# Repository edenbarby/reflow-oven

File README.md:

# reflow-oven
A DIY reflow oven with a little inspiration from the internet.

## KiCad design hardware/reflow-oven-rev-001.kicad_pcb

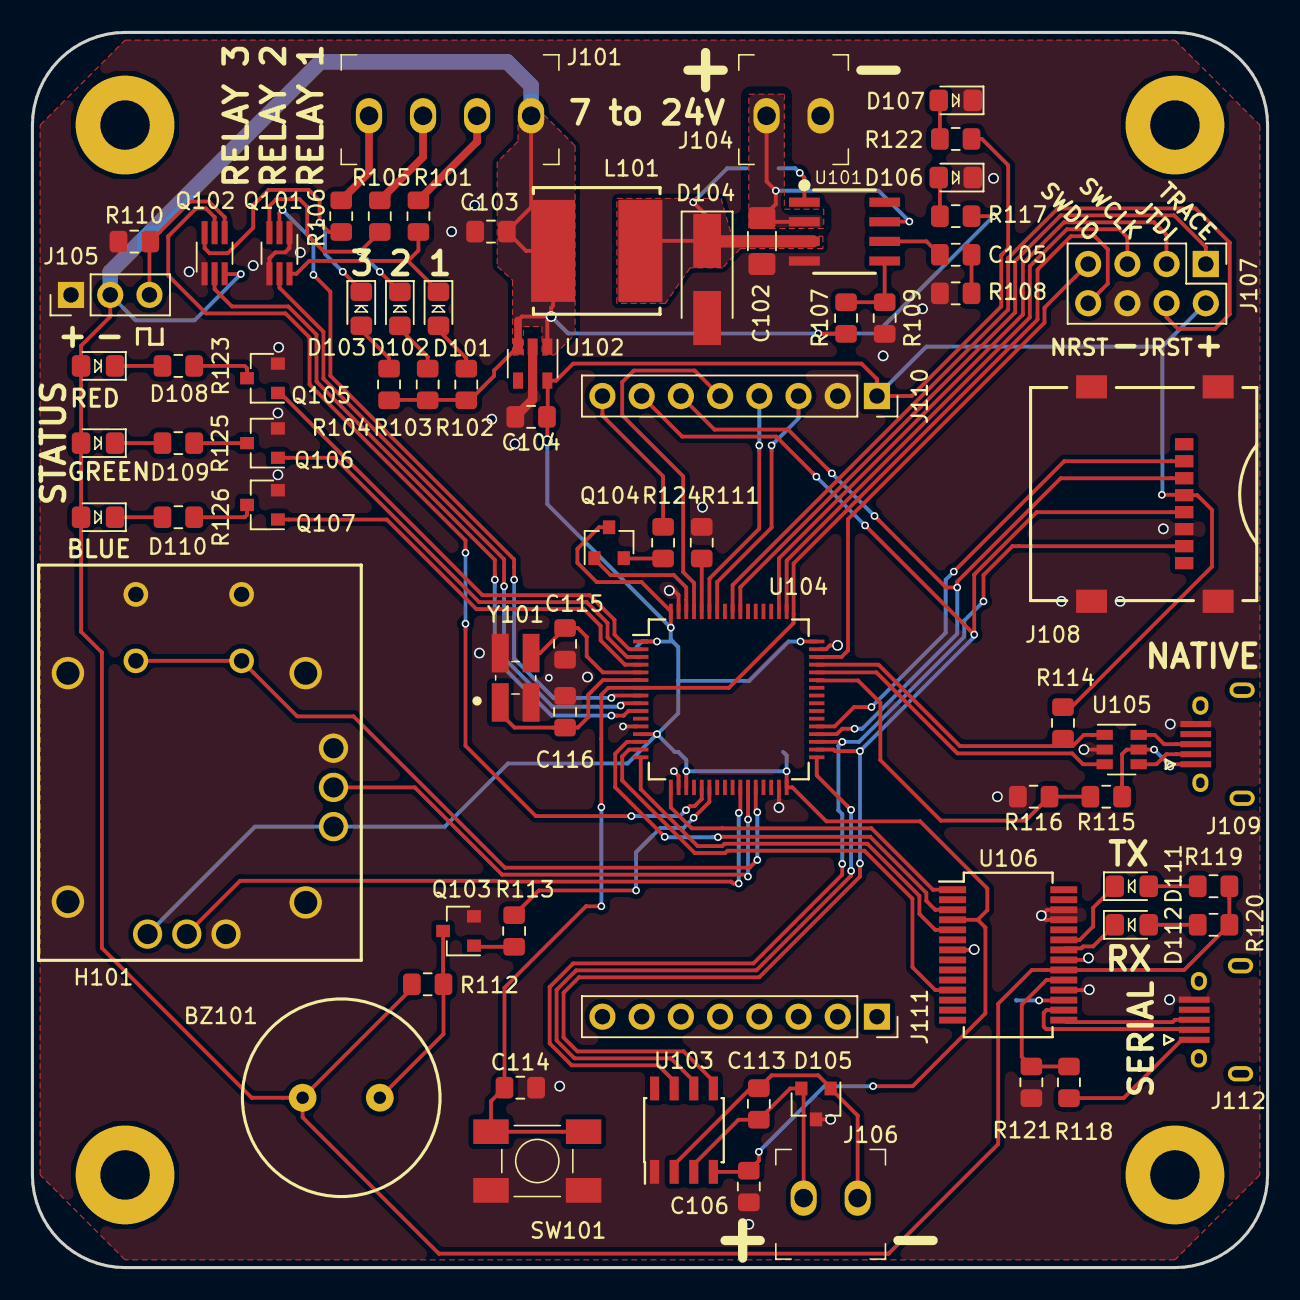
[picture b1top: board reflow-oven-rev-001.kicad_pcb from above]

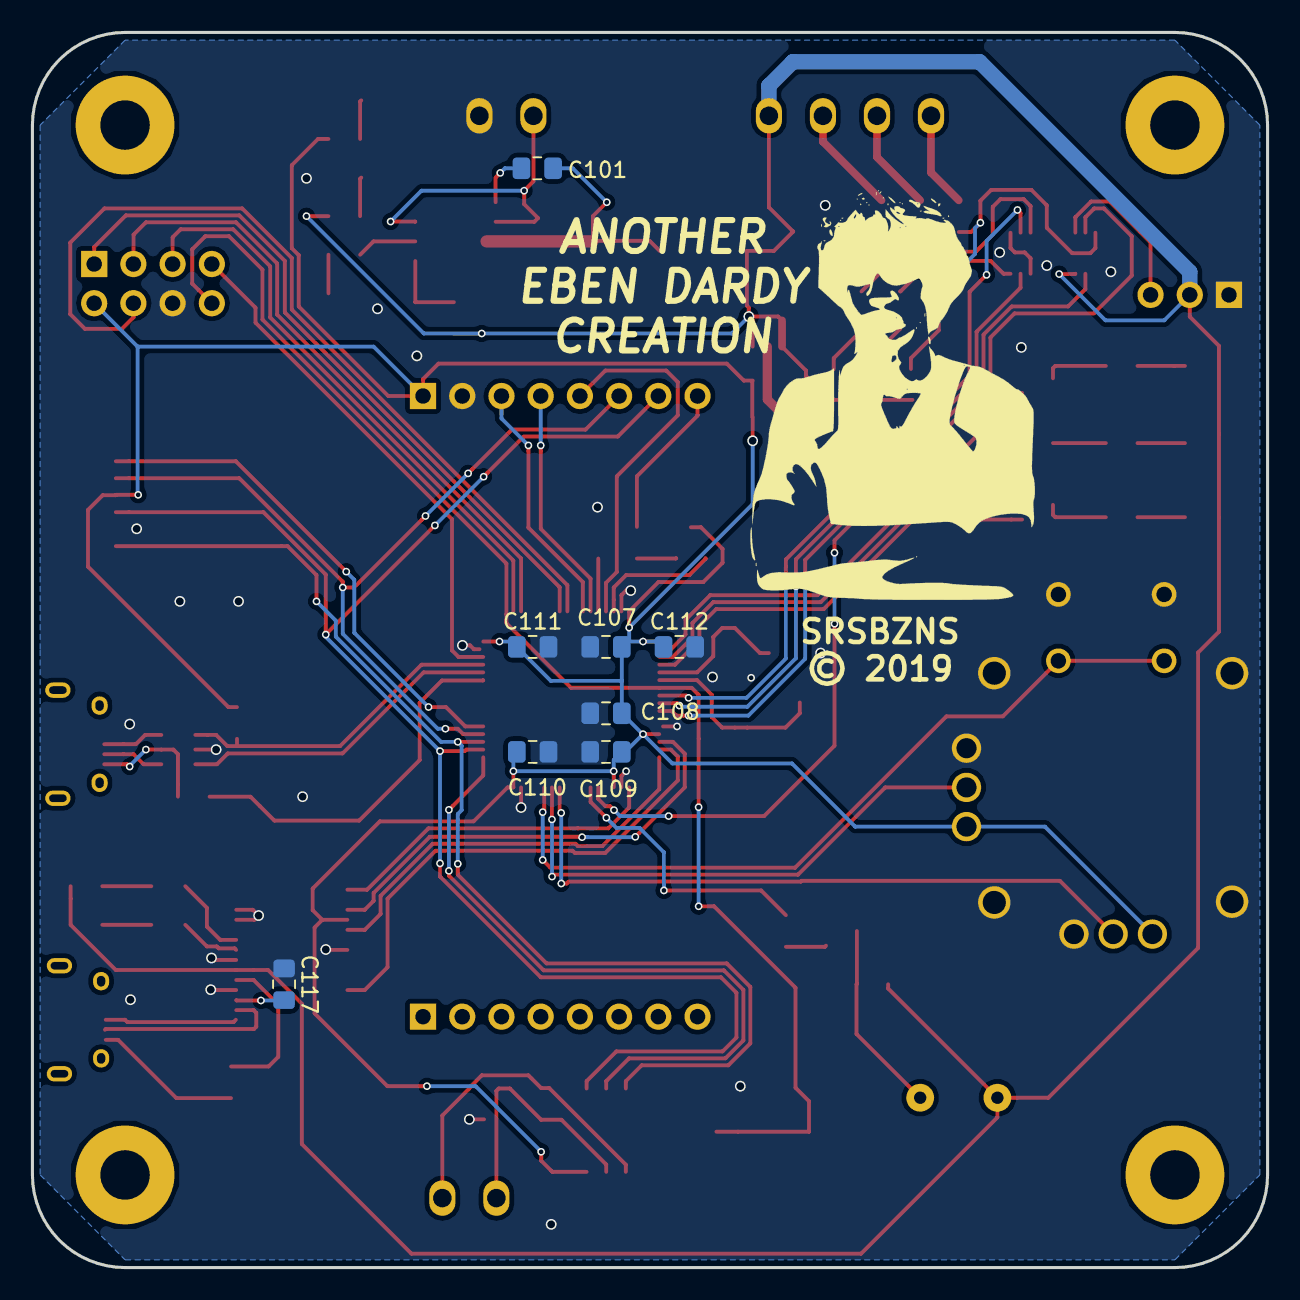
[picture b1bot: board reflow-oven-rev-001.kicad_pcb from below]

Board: 2 copper layers, 80.0 x 80.0 mm, 87 parts (8 on the bottom side), 81 nets.

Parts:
BZ101: Piezo Buzzer; PKM13EPYH4000-A0
C101, C113: 10n, 50V; C_0805_2012Metric_Pad1.15x1.40mm_HandSolder
C102: 10u, 50V; C_1206_3216Metric_Pad1.42x1.75mm_HandSolder
C103, C104: 4u7, 25V; C_0805_2012Metric_Pad1.15x1.40mm_HandSolder
C105: 2n2, 50V; C_0805_2012Metric_Pad1.15x1.40mm_HandSolder
C106, C107, C108, C109, C110, C111, C112, C114, C117: 100n; C_0805_2012Metric_Pad1.15x1.40mm_HandSolder
C115, C116: 10p; C_0805_2012Metric_Pad1.15x1.40mm_HandSolder
D101, D102, D103, D106, D107, D108: LED Red; LED_0805_2012Metric_Pad1.15x1.40mm_HandSolder
D104: Schottky, 40V, 3A; D_SMA_Handsoldering
D105: NUP2105L; SOT-23
D109, D111: LED Green; LED_0805_2012Metric_Pad1.15x1.40mm_HandSolder
D110, D112: LED Blue; LED_0805_2012Metric_Pad1.15x1.40mm_HandSolder
H101: Joystick; COM-09032
J101: Relays; Connector_Pheonix_WTB_Screw_3.5mm_4X1
J104: Power In; Connector_Pheonix_WTB_Screw_3.5mm_2X1
J105: Servo; PinHeader_1x03_P2.54mm_Vertical
J106: Thermocouple; Connector_Pheonix_WTB_Screw_3.5mm_2X1
J107: JTAG, SWD; PinHeader_2x04_P2.54mm_Vertical
J108: Micro SD Card; MEM2067-02-180-00-A
J109: USB Native; USB_Micro-B_Amphenol_10118194-0X0XLF
J110, J111: LCD 10168; PinSocket_1x08_P2.54mm_Vertical
J112: USB Serial; USB_Micro-B_Amphenol_10118194-0X0XLF
L101: 15u, 3.6A; SRN8040TA-150M
MH101, MH102, MH103, MH104: MountingHole; MountingHole_3.2mm_M3_Pad
Q101, Q102: SSM6N7002KFU; SOT-363_SC-70-6_Handsoldering
Q103, Q104, Q105, Q106, Q107: MMBT3904; SOT-23
R101, R102, R103, R104, R105, R106, R117, R119, R120, R122, R123, R124, R125, R126: 270R; R_0805_2012Metric_Pad1.15x1.40mm_HandSolder
R107, R108, R111, R121: 15k; R_0805_2012Metric_Pad1.15x1.40mm_HandSolder
R109, R110, R118: 5k6; R_0805_2012Metric_Pad1.15x1.40mm_HandSolder
R112, R113, R114: 1k5; R_0805_2012Metric_Pad1.15x1.40mm_HandSolder
R115, R116: 100k; R_0805_2012Metric_Pad1.15x1.40mm_HandSolder
SW101: Push Button; SW_SPST_CK_PTS647_4.5mm
U101: ACT4060A
U102: MIC5504-3.3YM5; SOT-23-5
U103: MAX31855KASA; SOIC-8_3.9x4.9mm_P1.27mm
U104: STM32F302R8Tx; LQFP-64_10x10mm_P0.5mm
U105: USBLC6-2SC6; SOT-23-6
U106: FT232RL; SSOP-28_5.3x10.2mm_P0.65mm
Y101: 12MHz; Crystal_SMD_2520-4Pin_2.5x2.0mm_HandSoldering

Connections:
+3V3: C104.1, C106.1, C107.1, C108.1, C109.1, C110.1, C111.1, C112.1, H101.1, H101.4, J107.2, J108.4, J110.1, Q104.3, R114.1, R122.1, U102.5, U103.4, U104.1, U104.13, U104.19, U104.32, U104.48, U104.64, U106.4
+5V: BZ101.1, C103.1, D108.2, D109.2, D110.2, J101.1, J105.2, L101.2, Q102.3, R102.1, R103.1, R104.1, R107.1, R112.1, R117.1, R119.1, R120.1, U102.1, U102.3, U106.20
/BUZZER: R113.2, U104.22
/FTDI_CTS: U104.15, U106.11
/FTDI_RTS: U104.14, U106.3
/FTDI_RX: U104.16, U106.5
/FTDI_TX: U104.17, U106.1
/JOYSTICK_BTN: H101.7, U104.28
/JOYSTICK_X: H101.2, U104.26
/JOYSTICK_Y: H101.5, U104.27
/JTCK_SWCLK: J107.5, U104.49
/JTDI: J107.3, U104.50
/JTDO_TRACESWO: J107.1, U104.55
/JTMS_SWDIO: J107.7, U104.46
/JTRST: J107.4, U104.56
/LCD_LED: Q104.1, U104.62
/LCD_MODE: J110.5, U104.61
/LCD_MOSI: J108.3, J110.6, U104.36
/LCD_SCLK: J108.5, J110.7, U103.5, U104.34
/LED_1: Q105.1, U104.2
/LED_2: Q106.1, U104.3
/LED_3: Q107.1, U104.4
/NRST: C114.1, J107.8, SW101.2, U104.7
/RELAY_1: Q101.2, U104.8
/RELAY_2: Q101.5, U104.9
/RELAY_3: Q102.2, U104.10
/RELAY_RET_1: J101.2, R101.2
/RELAY_RET_2: J101.3, R105.2
/SD_MISO: J108.7, U103.7, U104.35
/SERVO: Q102.5, U104.21
/USB_D+: R114.2, U104.45, U105.1
/USB_D-: U104.44, U105.3
/USB_VBUS_SENSE: R115.2, R116.1, U104.43
/~LCD_CS: J110.3, U104.58
/~LCD_RST: J110.4, U104.59
/~SD_CS: J108.2, U104.37
/~TC_CS: U103.6, U104.33
GND: C102.2, C103.2, C104.2, C106.2, C107.2, C108.2, C109.2, C110.2, C111.2, C112.2, C114.2, C115.2, C116.1, C117.1, D104.2, D105.3, D106.1, D107.1, H101.3, H101.6, H101.8, H101.9, J104.1, J105.1, J107.6, J108.6, J108.9, J109.5, J110.2, J112.5, Q101.1, Q101.4, Q102.1, Q103.2, Q105.2, Q106.2, Q107.2, R108.2, R109.2, R110.2, R111.2, R116.2, R121.2, SW101.1, U101.4, U102.2, U103.1, U104.12, U104.18, U104.31, U104.47, U104.63, U105.2, U106.7, U106.18, U106.21, U106.25, U106.26, Y101.2, Y101.4
unnamed: BZ101.2, Q103.3, R112.2
unnamed: C101.1, U101.1
unnamed: C101.2, D104.1, L101.1, U101.3
unnamed: C102.1, J104.2, U101.2, U101.7
unnamed: C105.1, U101.6
unnamed: C105.2, R108.1
unnamed: C113.1, D105.2, J106.1, U103.3
unnamed: C113.2, D105.1, J106.2, U103.2
unnamed: C115.1, U104.5, Y101.3
unnamed: C116.2, U104.6, Y101.1
unnamed: C117.2, U106.17
unnamed: D101.1, Q101.6, R101.1
unnamed: D101.2, R102.2
unnamed: D102.1, Q101.3, R105.1
unnamed: D102.2, R103.2
unnamed: D103.1, Q102.6, R106.1
unnamed: D103.2, R104.2
unnamed: D106.2, R117.2
unnamed: D107.2, R122.2
unnamed: D108.1, R123.1
unnamed: D109.1, R125.1
unnamed: D110.1, R126.1
unnamed: D111.1, U106.23
unnamed: D111.2, R119.2
unnamed: D112.1, U106.22
unnamed: D112.2, R120.2
unnamed: J101.4, R106.2
unnamed: J105.3, Q102.4, R110.1
unnamed: J109.2, U105.4
unnamed: J109.3, U105.6
unnamed: J110.8, R124.2
unnamed: J112.1, R118.1
unnamed: J112.2, U106.16
unnamed: J112.3, U106.15
unnamed: Q103.1, R113.1
unnamed: Q104.2, R124.1
unnamed: Q105.3, R123.2
unnamed: Q106.3, R125.2
unnamed: Q107.3, R126.2
unnamed: R107.2, R109.1, U101.5
unnamed: R111.1, U104.60
unnamed: R118.2, R121.1, U106.19
VBUS: J109.1, R115.1, U105.5

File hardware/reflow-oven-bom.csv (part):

"Source:","D:\repo\reflow-oven\hardware\reflow-oven-rev-001.sch"
"Date:","18/09/2019 8:32:10 AM"
"Tool:","Eeschema (5.0.0)"
"Generator:","D:\Program Files\KiCad\bin\scripting\plugins/bom_csv_grouped_by_value.py"
"Component Count:","87"

"Individual Components:"

"Item","Qty","Reference(s)","Value","LibPart","Footprint","Datasheet","Description","Digi-Key Part Number"
"","","BZ101","Piezo Buzzer","Device:Buzzer","my-library:PKM13EPYH4000-A0","","AUDIO PIEZO TRANSDUCER 30V TH","490-4698-1-ND"
"","","C101","10n, 50V","Device:C","Capacitor_SMD:C_0805_2012Metric_Pad1.15x1.40mm_HandSolder","","CAP CER 10000PF 50V X7R 0805","1276-1015-1-ND"
"","","C102","10u, 50V","Device:C","Capacitor_SMD:C_1206_3216Metric_Pad1.42x1.75mm_HandSolder","","CAP CER 10UF 50V X5R 1206","1276-6736-1-ND"
"","","C103","4u7, 25V","Device:C","Capacitor_SMD:C_0805_2012Metric_Pad1.15x1.40mm_HandSolder","","CAP CER 4.7UF 25V X5R 0805","732-7628-1-ND"
"","","C104","4u7, 25V","Device:C","Capacitor_SMD:C_0805_2012Metric_Pad1.15x1.40mm_HandSolder","","CAP CER 4.7UF 25V X5R 0805","732-7628-1-ND"
"","","C105","2n2, 50V","Device:C","Capacitor_SMD:C_0805_2012Metric_Pad1.15x1.40mm_HandSolder","","CAP CER 2200PF 50V X7R 0805","399-1151-1-ND"
"","","C106","100n","Device:C_Small","Capacitor_SMD:C_0805_2012Metric_Pad1.15x1.40mm_HandSolder","","CAP CER 0.1UF 50V X7R 0805","1276-2450-1-ND"
"","","C107","100n","Device:C_Small","Capacitor_SMD:C_0805_2012Metric_Pad1.15x1.40mm_HandSolder","","CAP CER 0.1UF 50V X7R 0805","1276-2450-1-ND"
"","","C108","100n","Device:C_Small","Capacitor_SMD:C_0805_2012Metric_Pad1.15x1.40mm_HandSolder","","CAP CER 0.1UF 50V X7R 0805","1276-2450-1-ND"
"","","C109","100n","Device:C_Small","Capacitor_SMD:C_0805_2012Metric_Pad1.15x1.40mm_HandSolder","","CAP CER 0.1UF 50V X7R 0805","1276-2450-1-ND"
"","","C110","100n","Device:C_Small","Capacitor_SMD:C_0805_2012Metric_Pad1.15x1.40mm_HandSolder","","CAP CER 0.1UF 50V X7R 0805","1276-2450-1-ND"
"","","C111","100n","Device:C_Small","Capacitor_SMD:C_0805_2012Metric_Pad1.15x1.40mm_HandSolder","","CAP CER 0.1UF 50V X7R 0805","1276-2450-1-ND"
"","","C112","100n","Device:C_Small","Capacitor_SMD:C_0805_2012Metric_Pad1.15x1.40mm_HandSolder","","CAP CER 0.1UF 50V X7R 0805","1276-2450-1-ND"
"","","C113","10n, 50V","Device:C_Small","Capacitor_SMD:C_0805_2012Metric_Pad1.15x1.40mm_HandSolder","","CAP CER 10000PF 50V X7R 0805","1276-1015-1-ND"
"","","C114","100n","Device:C_Small","Capacitor_SMD:C_0805_2012Metric_Pad1.15x1.40mm_HandSolder","","CAP CER 0.1UF 50V X7R 0805","1276-2450-1-ND"
"","","C115","10p","Device:C_Small","Capacitor_SMD:C_0805_2012Metric_Pad1.15x1.40mm_HandSolder","","CAP CER 10PF 50V C0G/NP0 0805","1276-1109-1-ND"
"","","C116","10p","Device:C_Small","Capacitor_SMD:C_0805_2012Metric_Pad1.15x1.40mm_HandSolder","","CAP CER 10PF 50V C0G/NP0 0805","1276-1109-1-ND"
"","","C117","100n","Device:C_Small","Capacitor_SMD:C_0805_2012Metric_Pad1.15x1.40mm_HandSolder","","CAP CER 0.1UF 50V X7R 0805","1276-2450-1-ND"
"","","D101","LED Red","Device:LED","LED_SMD:LED_0805_2012Metric_Pad1.15x1.40mm_HandSolder","","LED RED CLEAR 0805 SMD","732-4978-1-ND"
"","","D102","LED Red","Device:LED","LED_SMD:LED_0805_2012Metric_Pad1.15x1.40mm_HandSolder","","LED RED CLEAR 0805 SMD","732-4978-1-ND"
"","","D103","LED Red","Device:LED","LED_SMD:LED_0805_2012Metric_Pad1.15x1.40mm_HandSolder","","LED RED CLEAR 0805 SMD","732-4978-1-ND"
"","","D104","Schottky, 40V, 3A","Device:D_Schottky","Diode_SMD:D_SMA_Handsoldering","","DIODE SCHOTTKY 4A 100V SMA-2","NRVTSA4100T3GOSCT-ND"
"","","D105","NUP2105L","Power_Protection:NUP2105L","Package_TO_SOT_SMD:SOT-23","","TVS DIODE 24V 44V SOT23-3","NUP2105LT1GOSCT-ND"
"","","D106","LED Red","Device:LED","LED_SMD:LED_0805_2012Metric_Pad1.15x1.40mm_HandSolder","","LED RED CLEAR 0805 SMD","732-4978-1-ND"
"","","D107","LED Red","Device:LED","LED_SMD:LED_0805_2012Metric_Pad1.15x1.40mm_HandSolder","","LED RED CLEAR 0805 SMD","732-4978-1-ND"
"","","D108","LED Red","Device:LED","LED_SMD:LED_0805_2012Metric_Pad1.15x1.40mm_HandSolder","","LED RED CLEAR 0805 SMD","732-4978-1-ND"
"","","D109","LED Green","Device:LED","LED_SMD:LED_0805_2012Metric_Pad1.15x1.40mm_HandSolder","","LED GREEN CLEAR 0805 SMD","732-4986-1-ND"
"","","D110","LED Blue","Device:LED","LED_SMD:LED_0805_2012Metric_Pad1.15x1.40mm_HandSolder","","LED BLUE CLEAR 0805 SMD","732-4982-1-ND"
"","","D111","LED Green","Device:LED","LED_SMD:LED_0805_2012Metric_Pad1.15x1.40mm_HandSolder","","LED GREEN CLEAR 0805 SMD","732-4986-1-ND"
"","","D112","LED Blue","Device:LED","LED_SMD:LED_0805_2012Metric_Pad1.15x1.40mm_HandSolder","","LED BLUE CLEAR 0805 SMD","732-4982-1-ND"
"","","H101","Joystick","my-library:JOYSTICK_COM09032","my-library:COM-09032","","COM09032 JOYSTICK 10K OHM 2 AXIS TH","1568-1526-ND"
"","","J101","Relays","Connector:Screw_Terminal_01x04","my-library:Connector_Pheonix_WTB_Screw_3.5mm_4X1","","TERM BLK 4POS SIDE ENT 3.5MM PCB","277-1860-ND"
"","","J104","Power In","Connector:Screw_Terminal_01x02","my-library:Connector_Pheonix_WTB_Screw_3.5mm_2X1","","TERM BLK 2POS SIDE ENT 3.5MM PCB","277-1721-ND"
"","","J105","Servo","Connector_Generic:Conn_01x03","Connector_PinHeader_2.54mm:PinHeader_1x03_P2.54mm_Vertical","","CONN HEADER VERT 40POS 2.54MM","S1012EC-40-ND"
"","","J106","Thermocouple","Connector:Screw_Terminal_01x02","my-library:Connector_Pheonix_WTB_Screw_3.5mm_2X1","","TERM BLK 2POS SIDE ENT 3.5MM PCB","277-1721-ND"
"","","J107","JTAG, SWD","Connector_Generic:Conn_02x04_Odd_Even","Connector_PinHeader_2.54mm:PinHeader_2x04_P2.54mm_Vertical","","PIN HEADER 20P 2.54MM PITCH PLUG","2057-PH2-20-UA-ND"
"","","J108","Micro SD Card","Connector:Micro_SD_Card","my-library:MEM2067-02-180-00-A","","MICRO SD HINGED, SMT, 1.80MM PRO","2073-MEM2067-02-180-00-ACT-ND"
"","","J109","USB Native","my-library:USB_B_Micro","my-library:USB_Micro-B_Amphenol_10118194-0X0XLF","","CONN RCPT USB2.0 MICRO B SMD R/A","609-4618-1-ND"
"","","J110","LCD 10168","Connector_Generic:Conn_01x08","Connector_PinSocket_2.54mm:PinSocket_1x08_P2.54mm_Vertical","","CONN HDR 8POS 0.1 TIN PCB","S7006-ND"
"","","J111","LCD 10168","Connector_Generic:Conn_01x08","Connector_PinSocket_2.54mm:PinSocket_1x08_P2.54mm_Vertical","","CONN HDR 8POS 0.1 TIN PCB","S7006-ND"
"","","J112","USB Serial","my-library:USB_B_Micro","my-library:USB_Micro-B_Amphenol_10118194-0X0XLF","","CONN RCPT USB2.0 MICRO B SMD R/A","609-4618-1-ND"
"","","L101","15u, 3.6A","Device:L","my-library:SRN8040TA-150M","","FIXED IND 15UH 3.6A 50 MOHM SMD","SRN8040TA-150MCT-ND"
"","","MH101","MountingHole","Mechanical:MountingHole","MountingHole:MountingHole_3.2mm_M3_Pad","~","",""
"","","MH102","MountingHole","Mechanical:MountingHole","MountingHole:MountingHole_3.2mm_M3_Pad","~","",""
"","","MH103","MountingHole","Mechanical:MountingHole","MountingHole:MountingHole_3.2mm_M3_Pad","~","",""
"","","MH104","MountingHole","Mechanical:MountingHole","MountingHole:MountingHole_3.2mm_M3_Pad","~","",""
"","","Q101","SSM6N7002KFU","my-library:SSM6N7002KFU","Package_TO_SOT_SMD:SOT-363_SC-70-6_Handsoldering","","MOSFET 2N-CH 60V 0.3A","SSM6N7002KFULFCT-ND"
"","","Q102","SSM6N7002KFU","my-library:SSM6N7002KFU","Package_TO_SOT_SMD:SOT-363_SC-70-6_Handsoldering","","MOSFET 2N-CH 60V 0.3A","SSM6N7002KFULFCT-ND"
"","","Q103","MMBT3904","Transistor_BJT:MMBT3904","Package_TO_SOT_SMD:SOT-23","","TRANS NPN 40V 0.2A SOT23","MMBT3904TPMSCT-ND"
"","","Q104","MMBT3904","Transistor_BJT:MMBT3904","Package_TO_SOT_SMD:SOT-23","","TRANS NPN 40V 0.2A SOT23","MMBT3904TPMSCT-ND"
"","","Q105","MMBT3904","Transistor_BJT:MMBT3904","Package_TO_SOT_SMD:SOT-23","","TRANS NPN 40V 0.2A SOT23","MMBT3904TPMSCT-ND"
"","","Q106","MMBT3904","Transistor_BJT:MMBT3904","Package_TO_SOT_SMD:SOT-23","","TRANS NPN 40V 0.2A SOT23","MMBT3904TPMSCT-ND"
"","","Q107","MMBT3904","Transistor_BJT:MMBT3904","Package_TO_SOT_SMD:SOT-23","","TRANS NPN 40V 0.2A SOT23","MMBT3904TPMSCT-ND"
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
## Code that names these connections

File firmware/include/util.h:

#ifndef UTIL_H
#define UTIL_H

#include <stdint.h>

/* Peripheral Interface Definitions *******************************************/
// Timer 16 Channel 1
#define BUZZER_PORT GPIOA
#define BUZZER_PIN LL_GPIO_PIN_6 // AF1

#define FTDI_PORT GPIOA
#define FTDI_RTS LL_GPIO_PIN_0 // AF7
#define FTDI_CTS LL_GPIO_PIN_1 // AF7
#define FTDI_RX LL_GPIO_PIN_2  // AF7
#define FTDI_TX LL_GPIO_PIN_3  // AF7

#define LCD_PORT GPIOB
#define LCD_CS_PIN LL_GPIO_PIN_6
#define LCD_RST_PIN LL_GPIO_PIN_7
#define LCD_MODE_PIN LL_GPIO_PIN_8
#define LCD_BACKLIGHT_PIN LL_GPIO_PIN_9

#define RELAY_PORT GPIOC
#define RELAY_1_PIN LL_GPIO_PIN_0
#define RELAY_2_PIN LL_GPIO_PIN_1
#define RELAY_3_PIN LL_GPIO_PIN_2

#define SD_PORT GPIOC
#define SD_CS_PIN LL_GPIO_PIN_6

// Timer 2 Channel 1
#define SERVO_PORT GPIOA
#define SERVO_PIN LL_GPIO_PIN_5 // AF1

#define MAX31855_PORT GPIOB
#define MAX31855_CS_PIN LL_GPIO_PIN_12

/* Global Limits **************************************************************/
#define REFLOW_SAFE_MAX_TEMP_OVEN 300.0f
#define REFLOW_SAFE_MAX_TEMP_REF 60.0f // Based on maximum safe to touch temperature (according to a 3 second google search).
#define REFLOW_SAFE_MAX_TEMP_CPU 60.0f
#define REFLOW_SAFE_COOL_TEMP 60.0f
#define REFLOW_PROFILE_STEPS_MIN 2
#define REFLOW_PROFILE_STEPS_MAX 20
#define REFLOW_PROFILE_TIME_MAX 3600.0f // 1 hour.
#define REFLOW_PROFILE_TEMP_MIN 0.0f
#define REFLOW_PROFILE_TEMP_MAX 260.0f

/* Global Error Flags *********************************************************/
#define ERROR_TC_COM (1 << 0) // Thermocouple IC communications error.
#define ERROR_TC_FLT (1 << 1) // Thermocouple unknown fault.
#define ERROR_TC_OPN (1 << 2) // Thermocouple disconnected.
#define ERROR_TC_GND (1 << 3) // Thermocouple shorted to ground.
#define ERROR_TC_VCC (1 << 4) // Thermocouple shorted to VCC.
#define ERROR_TP_OVN (1 << 5) // Oven temperature exceeded maximum.
#define ERROR_TP_REF (1 << 6) // Thermocouple IC temperature exceeded maximum.

/* Global States **************************************************************/
#define OVEN_STATE_INIT 0
#define OVEN_STATE_IDLE 1
#define OVEN_STATE_SOAK_RAMP 2
#define OVEN_STATE_SOAK 3
#define OVEN_STATE_REFLOW_RAMP 4
#define OVEN_STATE_REFLOW 5

/* Global Data Types **********************************************************/
typedef struct
{
    float p;
    float i;
    float d;
    float i_max;
} pid_settings_t;

typedef struct
{
    float ramp_rate;
    float soak_time;
    float soak_temp;
    float reflow_time;
    float reflow_temp;
    pid_settings_t controller_ramp;
    pid_settings_t controller_fixed;
} reflow_profile_t;

typedef struct
{
    uint32_t errors;
    uint32_t state;
    float temp_oven;
    float temp_ref;
    float p_current;
    float i_current;
    float d_current;
    float power_current;
    reflow_profile_t profile;
} oven_context_t;

#endif // UTIL_H

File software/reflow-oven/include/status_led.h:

#ifndef STATUS_LED_H
#define STATUS_LED_H

#include "stm32f3xx_ll_gpio.h"

#define STATUS_LED_RED LL_GPIO_PIN_13   // LED_1
#define STATUS_LED_GREEN LL_GPIO_PIN_14 // LED_2
#define STATUS_LED_BLUE LL_GPIO_PIN_15  // LED_3
#define STATUS_LED_ALL (STATUS_LED_RED | STATUS_LED_GREEN | STATUS_LED_BLUE)

void status_led_init(void);
void status_led_set(uint32_t led);
void status_led_reset(uint32_t led);
void status_led_toggle(uint32_t led);

#endif // STATUS_LED_H

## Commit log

2020-06-08 Hardware designs are complete and fabricated (mostly). Software started, LCD drivers fairly fuctional at the moment.
2020-06-24 Begun migration of code into VisualStudioCode+PlatformIO IDE. Clock configuration and basic system timing done.
2020-06-26 Added SPI2 and LCD drivers (they are mostly functional), added additional warning flags to build system.
2020-06-26 Added basic polling USART2 drivers. Will eventually migrate them to interrupt driven but this will do for the time being.
2020-07-04 Expanded spi driver to handle multiple users with different settings. Added thermocouple drivers. Disabled overrun detection on USART because it seems to block reception of terminal input if there is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
2020-07-16 Modified usart2 drivers so that they're now interrupt driven with an internal ring buffer for rx and tx (also added a ring buffer module). Added a consistent overhead byte stuffing module for furture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
2020-07-16 Adjusted code style. Added python script to help display expected LCD output using GDB dump of frame buffer.
2020-10-25 Added serial driver which leverages ring buffers for interrupt safe buffering and COBS for packet delineation. Adjusted max31855 driver to report temps in int16 so it's easier to pass over serial to 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
2020-10-25 Created simple app to interface with reflow oven from a PC, leveraging the tkinter and matplotlib library. The app is seperated into front/back-end with reflowoven.py handling comms to the oven direc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
2021-02-01 Comms refactor, restructured program flow to utilise state machines more effectively.
2021-05-14 Simplified serial comms with between the app and oven, max31855 temp monitoring is now handled in the max31855_task which incorporates some smoothing, temperature control and reflow profile changed f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
2021-05-22 Removed old firmware /software/f410rb, moved /software/reflow-oven to /firmware and /software/python-app to /app.

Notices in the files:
hardware/reflow-oven-rev-001.kicad_pcb:
© 2019
